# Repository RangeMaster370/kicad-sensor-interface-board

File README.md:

# SIB-1 sensor-interface board in KiCad

A small 2-layer board, designed in KiCad 7 and broken into four functional stages: (1) reverse-polarity protected 5 V input and 3.3 V LDO, (2) ATmega328P microcontroller with ISP and status LED, (3) ratiometric NTC front end with a Sallen–Key anti-alias filter, (4) I²C temperature sensor, calibration EEPROM, I²C and UART connectors. All symbols and footprints come from a custom library built for the board. The design is described once in `src/sib/design.py`; Python scripts generate the schematic, library, PCB and outputs with KiCad's own tools, and the tests check KiCad's exported netlist back against that description.

| Question | Method | Result (see `results/REPORT.md`) |
|---|---|---|
| Does the schematic say what the design says? | KiCad netlist export compared net-by-net with `design.py` | 0 differences over 22 nets and 15 no-connect pins |
| Would ERC flag anything? | ERC-style rules on the netlist (undriven power, single-pin nets, output conflicts) | 0 problems |
| Do symbols and footprints agree? | pin numbers vs pad numbers for all 36 placed parts | all match |
| Is the board manufacturable as drawn? | KiCad DRC (clearance 0.2 mm, edge 0.5 mm, courtyards, solder mask) | 0 errors, 0 warnings, 0 unconnected pads |
| How much routing? | Freerouting autorouter, GND pour on the bottom layer | 296 track segments, 35 vias, 698 mm of track |
| Why these parts? | component-selection table with requirement, choice, evidence, alternatives | 9 key parts, linked to the SPICE project results |

## Run

```sh
pip install -r requirements.txt   # plus KiCad 7, Java and Freerouting (see requirements.txt)
python3 -m unittest discover -s tests -v
python3 src/run_all.py            # regenerates hardware/ and results/ (about 40 s)
```

Open `hardware/sib.kicad_pro` in KiCad 7 or later to inspect or edit the schematic and PCB interactively.

## Structure

```
src/sib/design.py      parts, pin-to-net maps, stages, component-selection notes (single design source)
src/sib/symbols.py     custom symbol library (SIB.kicad_sym)
src/sib/footprints.py  custom footprint library (SIB.pretty) from package land-pattern dimensions
src/sib/schematic.py   hierarchical schematic: root + one sheet per functional stage
src/sib/checks.py      netlist comparison and ERC-style rules
src/sib/pcb.py         pcbnew placement by stage, Freerouting round trip, GND pour, DRC
src/run_all.py         full rebuild, Gerber/drill zip, BOM, renders, summary.json, REPORT.md
hardware/              KiCad project (schematic, PCB, library tables, library)
results/               schematic.pdf, BOM, component selection, DRC report, fabrication zip, plots
tests/                 13 checks
```

## Scope

Design and verification in KiCad only: the board has not been fabricated, assembled or bench-tested. Land patterns use nominal IPC-style dimensions for each package, and the autorouted layout favours completeness over hand-routed quality (see `docs/METHOD.md`). Companion projects: `sensor-frontend-spice-verification` (ngspice stage verification) and `avr-bringup-firmware-sim` (C bring-up firmware, simulated).

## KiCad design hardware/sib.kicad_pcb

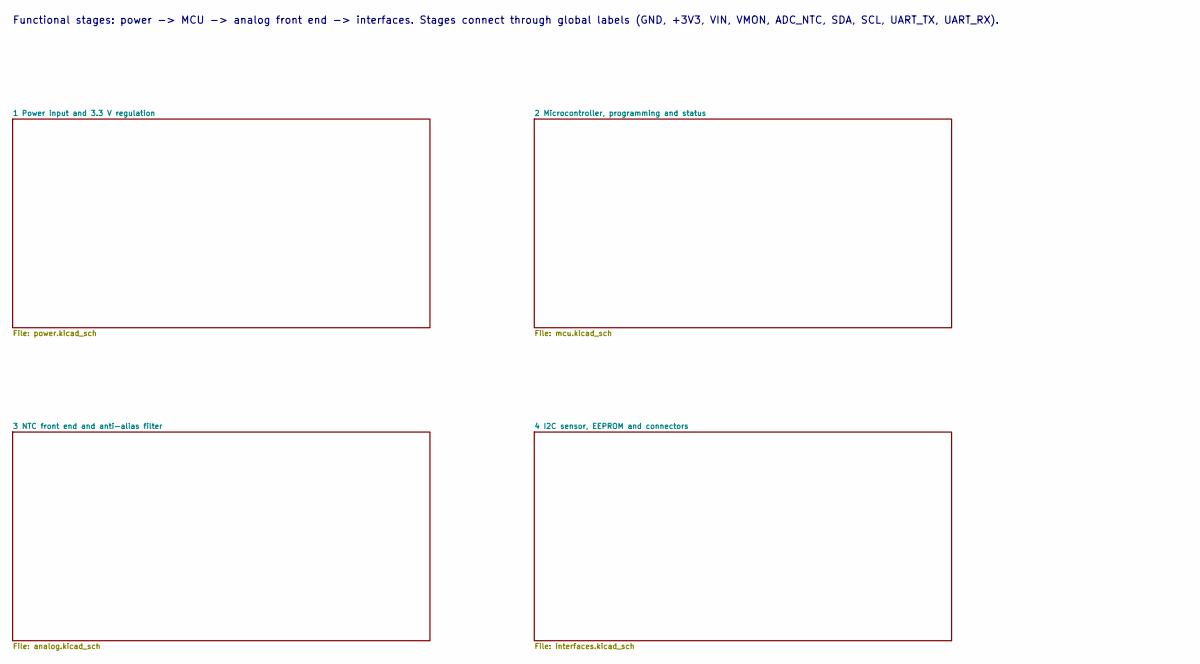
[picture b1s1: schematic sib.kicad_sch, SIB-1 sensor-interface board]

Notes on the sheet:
Functional stages: power -> MCU -> analog front end -> interfaces. Stages connect through global labels (GND, +3V3, VIN, VMON, ADC_NTC, SDA, SCL, UART_TX, UART_RX).

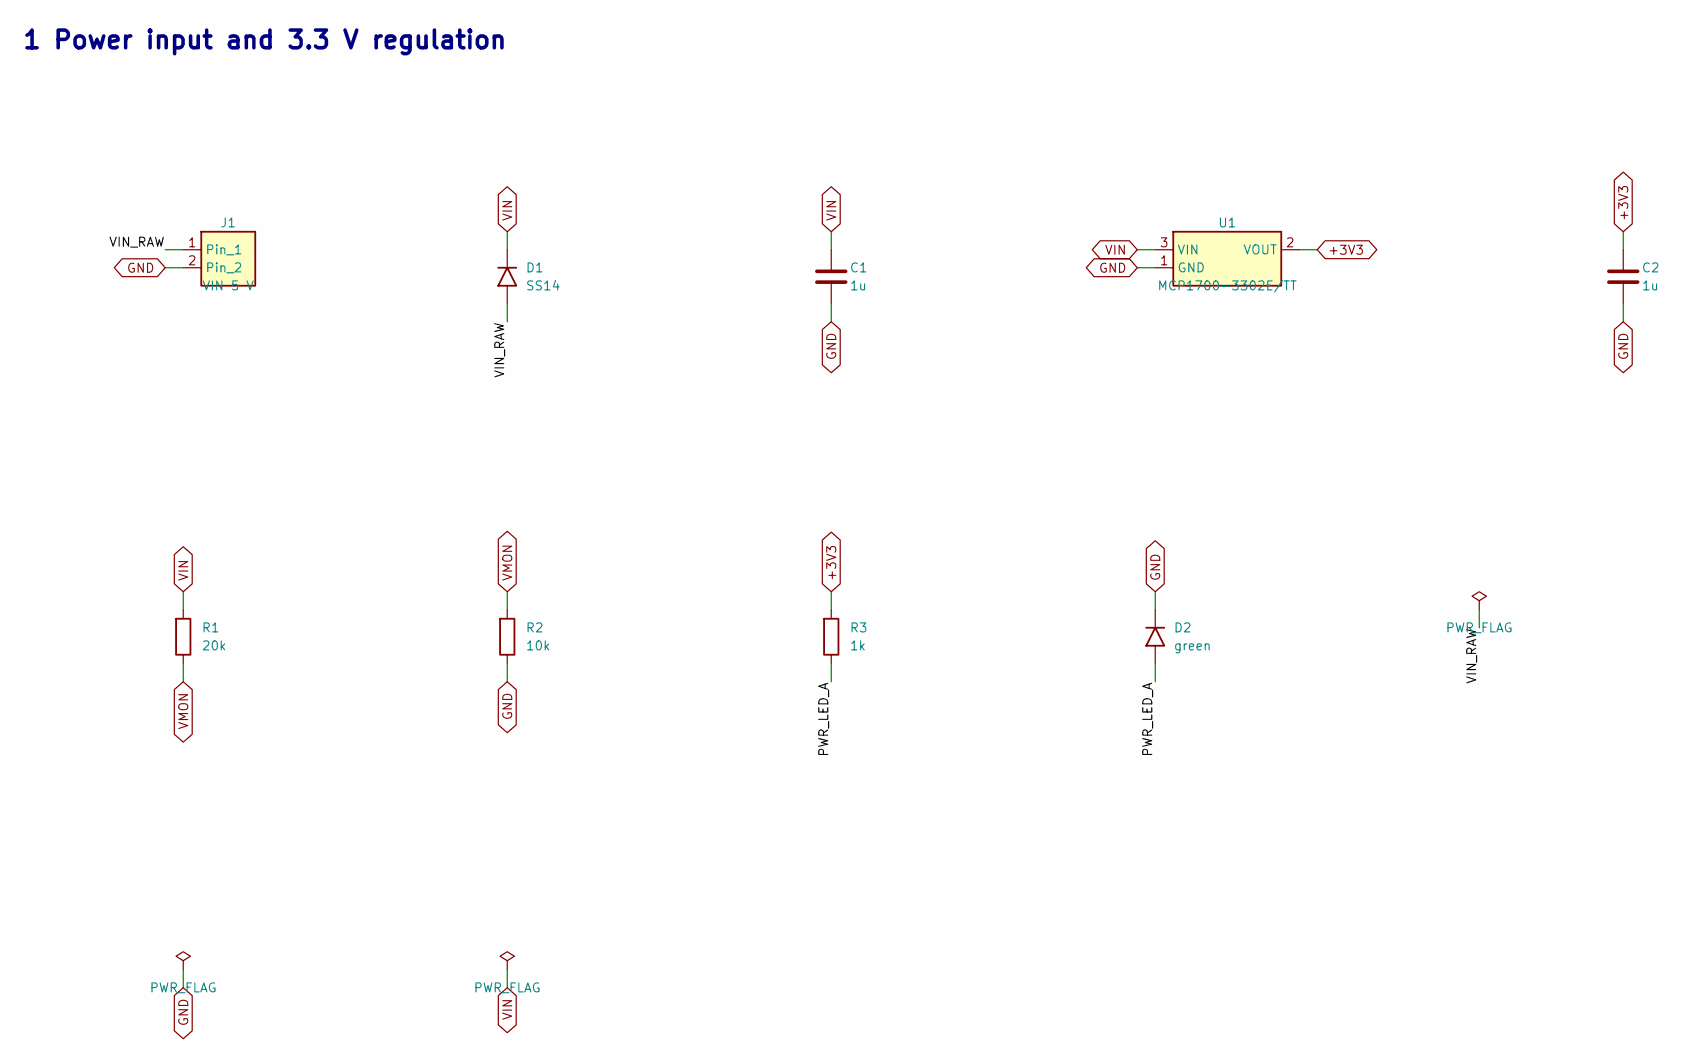
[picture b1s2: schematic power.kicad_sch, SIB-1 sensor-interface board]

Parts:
C1, C2: 1u; C_0603; MPN GRM188R61E105KA12
D1: SS14; D_SMA; MPN SS14
D2: green; LED_0603; MPN LTST-C191KGKT
J1: VIN 5 V; PinHeader_1x02_P2.54mm; MPN 2.54 mm header
R1: 20k; R_0603; MPN RC0603FR-0720KL
R2: 10k; R_0603; MPN RC0603FR-0710KL
R3: 1k; R_0603; MPN RC0603FR-071KL
U1: MCP1700-3302E/TT; SOT-23; MPN MCP1700T-3302E/TT

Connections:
+3V3: C2.1, R3.1, U1.2 (VOUT); also elsewhere on the board
GND: C1.2, C2.2, D2.1 (K), J1.2, R2.2, U1.1 (GND); also elsewhere on the board
PWR_LED_A: D2.2 (A), R3.2
VIN: C1.1, D1.1 (K), R1.1, U1.3 (VIN)
VIN_RAW: D1.2 (A), J1.1
VMON: R1.2, R2.1; also elsewhere on the board

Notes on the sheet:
1 Power input and 3.3 V regulation

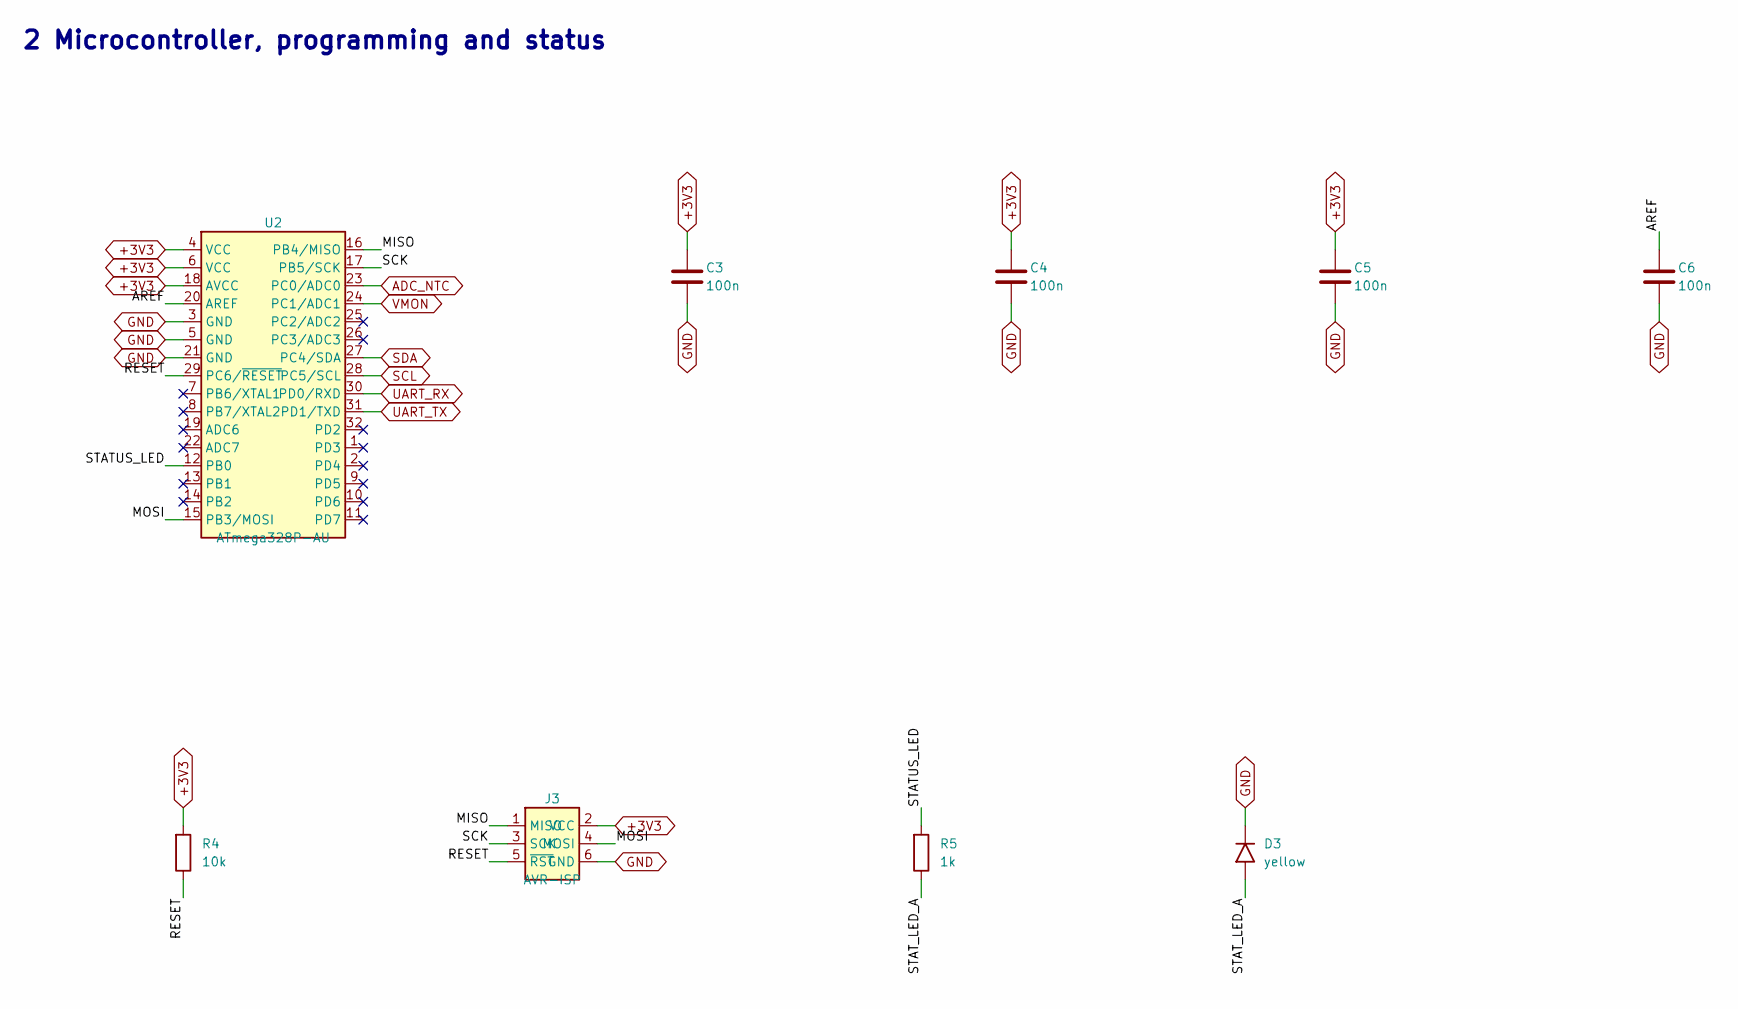
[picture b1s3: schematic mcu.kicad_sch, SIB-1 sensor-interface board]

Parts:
C3, C4, C5, C6: 100n; C_0603; MPN GRM188R71H104KA93
D3: yellow; LED_0603; MPN LTST-C191KSKT
J3: AVR-ISP; PinHeader_2x03_P2.54mm; MPN 2x3 header
R4: 10k; R_0603; MPN RC0603FR-0710KL
R5: 1k; R_0603; MPN RC0603FR-071KL
U2: ATmega328P-AU; TQFP-32_7x7mm_P0.8mm; MPN ATMEGA328P-AU

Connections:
+3V3: C3.1, C4.1, C5.1, J3.2 (VCC), R4.1, U2.4 (VCC), U2.6 (VCC), U2.18 (AVCC); also elsewhere on the board
ADC_NTC: U2.23 (PC0/ADC0); also elsewhere on the board
AREF: C6.1, U2.20 (AREF)
GND: C3.2, C4.2, C5.2, C6.2, D3.1 (K), J3.6 (GND), U2.3 (GND), U2.5 (GND), U2.21 (GND); also elsewhere on the board
MISO: J3.1 (MISO), U2.16 (PB4/MISO)
MOSI: J3.4 (MOSI), U2.15 (PB3/MOSI)
RESET: J3.5 (~RST), R4.2, U2.29 (PC6/~RESET)
SCK: J3.3 (SCK), U2.17 (PB5/SCK)
SCL: U2.28 (PC5/SCL); also elsewhere on the board
SDA: U2.27 (PC4/SDA); also elsewhere on the board
STATUS_LED: R5.1, U2.12 (PB0)
STAT_LED_A: D3.2 (A), R5.2
UART_RX: U2.30 (PD0/RXD); also elsewhere on the board
UART_TX: U2.31 (PD1/TXD); also elsewhere on the board
VMON: U2.24 (PC1/ADC1); also elsewhere on the board

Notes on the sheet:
2 Microcontroller, programming and status

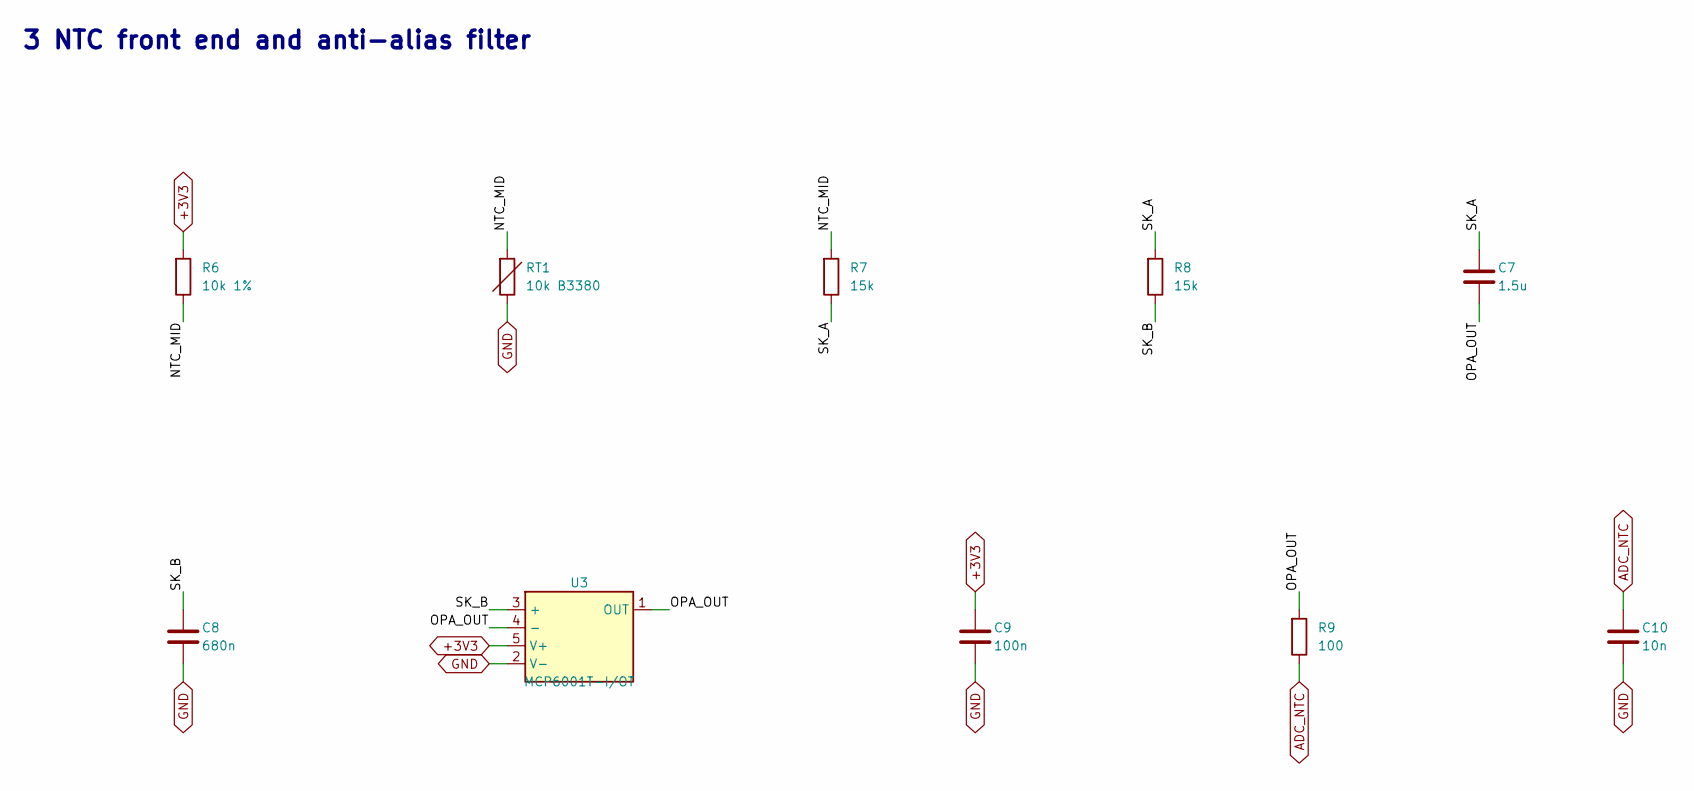
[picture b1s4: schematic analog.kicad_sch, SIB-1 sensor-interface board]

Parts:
C7: 1.5u; C_0805; MPN GRM21BR71C155KA01
C8: 680n; C_0603; MPN GRM188R71C684KA01
C9: 100n; C_0603; MPN GRM188R71H104KA93
C10: 10n; C_0603; MPN GRM188R71H103KA01
R6: 10k 1%; R_0603; MPN RC0603FR-0710KL
R7, R8: 15k; R_0603; MPN RC0603FR-0715KL
R9: 100; R_0603; MPN RC0603FR-07100RL
RT1: 10k B3380; R_0603; MPN NCP18XH103F03RB
U3: MCP6001T-I/OT; SOT-23-5; MPN MCP6001T-I/OT

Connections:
+3V3: C9.1, R6.1, U3.5 (V+); also elsewhere on the board
ADC_NTC: C10.1, R9.2; also elsewhere on the board
GND: C8.2, C9.2, C10.2, RT1.2, U3.2 (V-); also elsewhere on the board
NTC_MID: R6.2, R7.1, RT1.1
OPA_OUT: C7.2, R9.1, U3.1 (OUT), U3.4 (-)
SK_A: C7.1, R7.2, R8.1
SK_B: C8.1, R8.2, U3.3 (+)

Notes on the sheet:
3 NTC front end and anti-alias filter

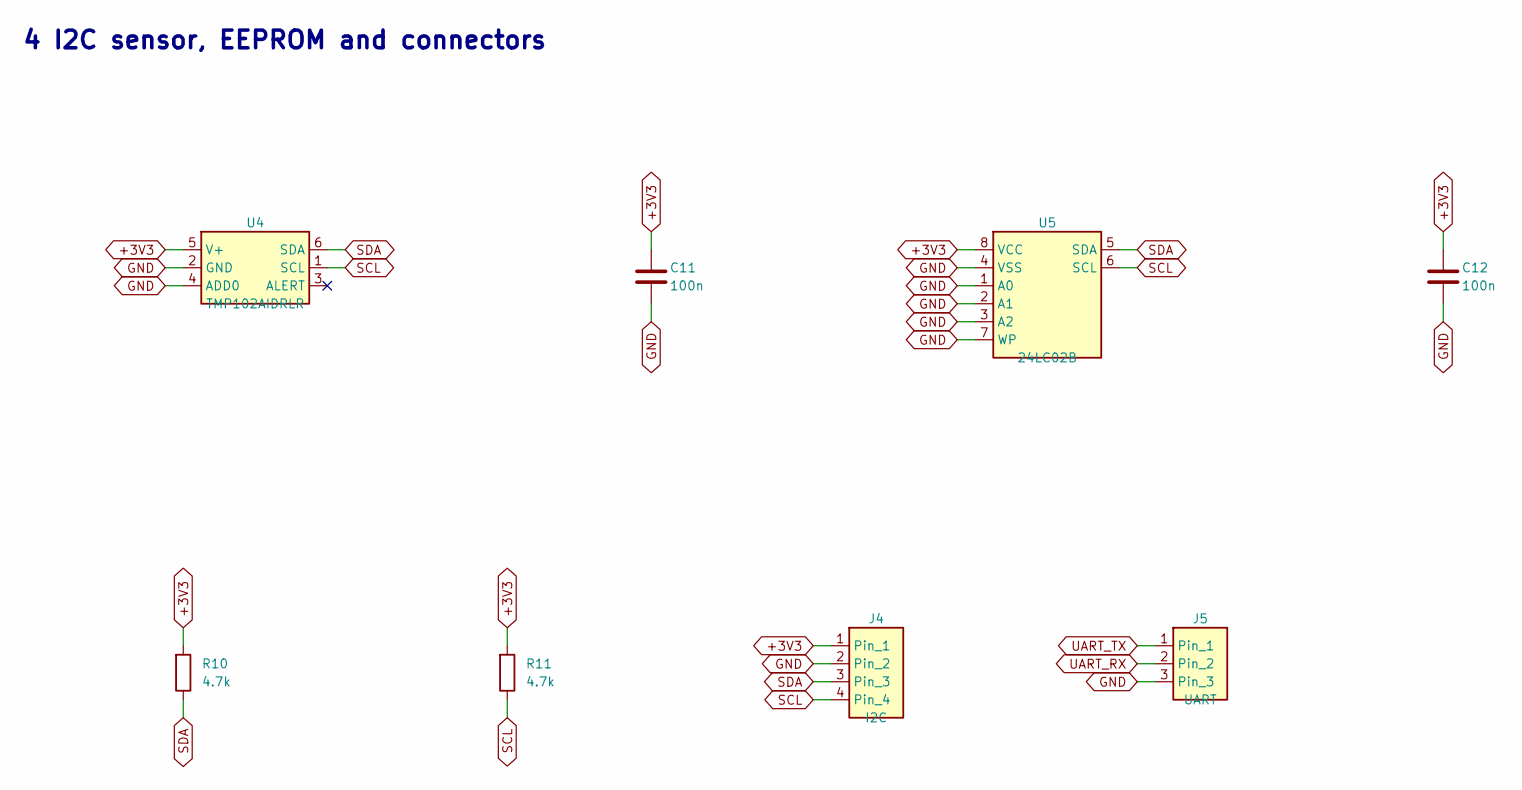
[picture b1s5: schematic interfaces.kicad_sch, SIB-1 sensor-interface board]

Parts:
C11, C12: 100n; C_0603; MPN GRM188R71H104KA93
J4: I2C; PinHeader_1x04_P2.54mm; MPN 2.54 mm header
J5: UART; PinHeader_1x03_P2.54mm; MPN 2.54 mm header
R10, R11: 4.7k; R_0603; MPN RC0603FR-074K7L
U4: TMP102AIDRLR; SOT-563; MPN TMP102AIDRLR
U5: 24LC02B; SOIC-8_3.9x4.9mm_P1.27mm; MPN 24LC02BT-I/SN

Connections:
+3V3: C11.1, C12.1, J4.1, R10.1, R11.1, U4.5 (V+), U5.8 (VCC); also elsewhere on the board
GND: C11.2, C12.2, J4.2, J5.3, U4.2 (GND), U4.4 (ADD0), U5.1 (A0), U5.2 (A1), U5.3 (A2), U5.4 (VSS), U5.7 (WP); also elsewhere on the board
SCL: J4.4, R11.2, U4.1 (SCL), U5.6 (SCL); also elsewhere on the board
SDA: J4.3, R10.2, U4.6 (SDA), U5.5 (SDA); also elsewhere on the board
UART_RX: J5.2; also elsewhere on the board
UART_TX: J5.1; also elsewhere on the board

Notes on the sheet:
4 I2C sensor, EEPROM and connectors

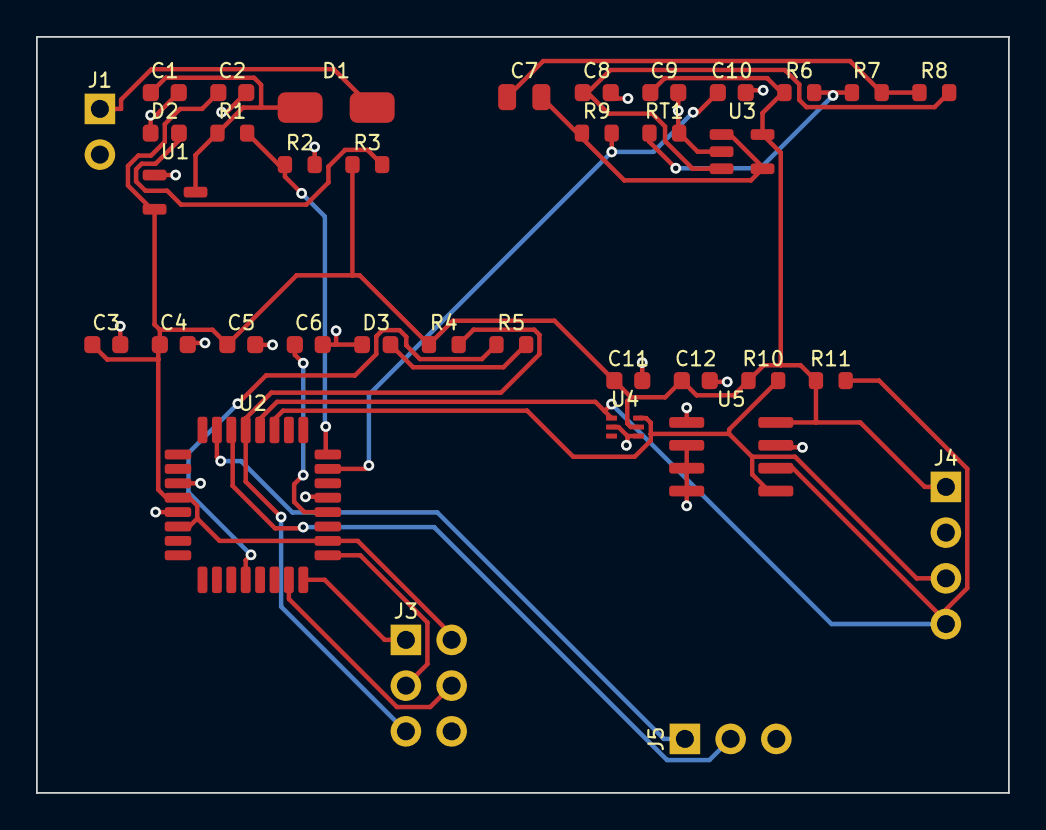
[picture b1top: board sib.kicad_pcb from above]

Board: 2 copper layers, 54.0 x 42.0 mm, 36 parts (0 on the bottom side), 22 nets.

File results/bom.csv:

refs,qty,value,footprint,mpn,stage,role
C1 C2,2,1u,C_0603,GRM188R61E105KA12,power,LDO input capacitor; LDO output capacitor
C10,1,10n,C_0603,GRM188R71H103KA01,analog,ADC charge reservoir
C3 C4 C5 C6 C9 C11 C12,7,100n,C_0603,GRM188R71H104KA93,mcu,VCC decoupling; AVCC decoupling; AREF capacitor; Op-amp decoupling; TMP102 decoupling; EEPROM decoupling
C7,1,1.5u,C_0805,GRM21BR71C155KA01,analog,Sallen-Key C1
C8,1,680n,C_0603,GRM188R71C684KA01,analog,Sallen-Key C2
D1,1,SS14,D_SMA,SS14,power,Reverse-polarity protection
D2,1,green,LED_0603,LTST-C191KGKT,power,Power LED
D3,1,yellow,LED_0603,LTST-C191KSKT,mcu,Status LED
J1,1,VIN 5 V,PinHeader_1x02_P2.54mm,2.54 mm header,power,Supply input
J3,1,AVR-ISP,PinHeader_2x03_P2.54mm,2x3 header,mcu,ISP programming
J4,1,I2C,PinHeader_1x04_P2.54mm,2.54 mm header,interfaces,I2C expansion
J5,1,UART,PinHeader_1x03_P2.54mm,2.54 mm header,interfaces,UART debug port
R1,1,20k,R_0603,RC0603FR-0720KL,power,Supply monitor divider top
R10 R11,2,4.7k,R_0603,RC0603FR-074K7L,interfaces,SDA pull-up; SCL pull-up
R2 R4,2,10k,R_0603,RC0603FR-0710KL,power,Supply monitor divider bottom; Reset pull-up
R3 R5,2,1k,R_0603,RC0603FR-071KL,power,Power LED resistor; Status LED resistor
R6,1,10k 1%,R_0603,RC0603FR-0710KL,analog,NTC divider top
R7 R8,2,15k,R_0603,RC0603FR-0715KL,analog,Sallen-Key R1; Sallen-Key R2
R9,1,100,R_0603,RC0603FR-07100RL,analog,Isolation resistor
RT1,1,10k B3380,R_0603,NCP18XH103F03RB,analog,Board temperature sensor
U1,1,MCP1700-3302E/TT,SOT-23,MCP1700T-3302E/TT,power,3.3 V LDO
U2,1,ATmega328P-AU,TQFP-32_7x7mm_P0.8mm,ATMEGA328P-AU,mcu,Microcontroller
U3,1,MCP6001T-I/OT,SOT-23-5,MCP6001T-I/OT,analog,Buffer op-amp
U4,1,TMP102AIDRLR,SOT-563,TMP102AIDRLR,interfaces,"Digital temperature sensor, address 0x48"
U5,1,24LC02B,SOIC-8_3.9x4.9mm_P1.27mm,24LC02BT-I/SN,interfaces,"Calibration EEPROM, address 0x50"

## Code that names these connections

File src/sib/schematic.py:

"""Generate the hierarchical KiCad 7 schematic: a root sheet plus one sheet per functional stage.

Each pin gets a short wire stub ending in a net label (local within a stage, global between
stages) or a no-connect marker. KiCad's own netlist export is then compared with design.py.
"""
from __future__ import annotations

import math
import uuid
from pathlib import Path

from . import design, symbols

NS = uuid.UUID("5b1a1d1e-0000-4000-8000-0000000051b1")
PROJECT = "sib"
G = 1.27
STUB = 2.54
FONT = "(effects (font (size 1.27 1.27)))"
HIDE = "(effects (font (size 1.27 1.27)) hide)"


def uid(*key) -> str:
    return str(uuid.uuid5(NS, "/".join(map(str, key))))


def snap(v: float) -> float:
    return round(round(v / G) * G, 4)


ROOT_UUID = uid("root")
SHEET_UUID = {name: uid("sheet", name) for name, _ in design.SHEETS}


class SheetWriter:
    def __init__(self, sheet: str, syms: dict):
        self.sheet, self.syms, self.items, self.used = sheet, syms, [], {}

    def wire(self, a, b):
        self.items.append(f'(wire (pts (xy {a[0]:g} {a[1]:g}) (xy {b[0]:g} {b[1]:g})) '
                          f'(stroke (width 0) (type default)) (uuid {uid(self.sheet, "w", a, b)}))')

    def label(self, net, at, out):
        ang, just = {(-1, 0): (180, "right"), (1, 0): (0, "left"), (0, -1): (90, "left"), (0, 1): (270, "right")}[out]
        if net in design.GLOBAL_NETS:
            self.items.append(
                f'(global_label "{net}" (shape bidirectional) (at {at[0]:g} {at[1]:g} {ang}) (fields_autoplaced) '
                f'(effects (font (size 1.27 1.27)) (justify {just})) (uuid {uid(self.sheet, "gl", net, at)}) '
                f'(property "Intersheetrefs" "${{INTERSHEET_REFS}}" (at {at[0]:g} {at[1]:g} 0) {HIDE}))')
        else:
            self.items.append(f'(label "{net}" (at {at[0]:g} {at[1]:g} {ang}) (fields_autoplaced) '
                              f'(effects (font (size 1.27 1.27)) (justify {just} bottom)) '
                              f'(uuid {uid(self.sheet, "l", net, at)}))')

    def no_connect(self, at):
        self.items.append(f'(no_connect (at {at[0]:g} {at[1]:g}) (uuid {uid(self.sheet, "nc", at)}))')

    def place(self, part: design.Part, sx: float, sy: float):
        _, pin_pos = self.syms[part.symbol]
        self.used[part.symbol] = True
        ys = [-p[1] for p in pin_pos.values()]
        top = sy + min(ys) - 2 * G
        props = [("Reference", part.ref, (sx, snap(top - G)), part.ref.startswith("#")),
                 ("Value", part.value, (sx, snap(sy + max(ys) + 2 * G)), False),
                 ("Footprint", f"SIB:{part.footprint}" if part.footprint else "", (sx, sy), True),
                 ("Datasheet", "", (sx, sy), True),
                 ("MPN", part.mpn, (sx, sy), True)]
        if len(pin_pos) == 2 and part.symbol != "Conn_01x02":
            props[0] = ("Reference", part.ref, (snap(sx + 2.54), snap(sy - G)), part.ref.startswith("#"))
            props[1] = ("Value", part.value, (snap(sx + 2.54), snap(sy + G)), False)
        ptxt = " ".join(
            f'(property "{k}" "{v}" (at {x:g} {y:g} 0) '
            f'{HIDE if hidden else ("(effects (font (size 1.27 1.27)) (justify left))" if len(pin_pos) == 2 and k in ("Reference", "Value") and part.symbol != "Conn_01x02" else FONT)})'
            for k, v, (x, y), hidden in props)
        pins = " ".join(f'(pin "{n}" (uuid {uid(self.sheet, part.ref, "pin", n)}))' for n in pin_pos)
        in_bom = "yes" if part.in_bom else "no"
        on_board = "no" if part.ref.startswith("#") else "yes"
        self.items.append(
            f'(symbol (lib_id "SIB:{part.symbol}") (at {sx:g} {sy:g} 0) (unit 1) (in_bom {in_bom}) '
            f'(on_board {on_board}) (dnp no) (fields_autoplaced) (uuid {uid(self.sheet, part.ref)}) {ptxt} {pins} '
            f'(instances (project "{PROJECT}" (path "/{ROOT_UUID}/{SHEET_UUID[self.sheet]}" '
            f'(reference "{part.ref}") (unit 1)))))')
        for num, (px, py, ang) in pin_pos.items():
            end = (snap(sx + px), snap(sy - py))
            out = (-round(math.cos(math.radians(ang))), round(math.sin(math.radians(ang))))
            net = part.pins.get(num)
            if net is None:
                self.no_connect(end)
                continue
            tip = (snap(end[0] + out[0] * STUB), snap(end[1] + out[1] * STUB))
            self.wire(end, tip)
            self.label(net, tip, out)

    def text(self, s, at, size=2.0):
        self.items.append(f'(text "{s}" (at {at[0]:g} {at[1]:g} 0) '
                          f'(effects (font (size {size:g} {size:g}) bold) (justify left bottom)) '
                          f'(uuid {uid(self.sheet, "t", s)}))')

    def render(self, title: str) -> str:
        lib = "\n    ".join(symbols.all_symbols(prefix="SIB:")[n][0] for n in sorted(self.used))
        return (f'(kicad_sch (version 20230121) (generator sib_schgen)\n  (uuid {SHEET_UUID[self.sheet]})\n'
                f'  (paper "A4")\n  (title_block (title "SIB-1 sensor-interface board") (comment 1 "{title}"))\n'
                f'  (lib_symbols\n    {lib}\n  )\n  ' + "\n  ".join(self.items) + "\n)\n")


def _extent(pin_pos):
    xs = [p[0] for p in pin_pos.values()]
    ys = [-p[1] for p in pin_pos.values()]
    return min(xs), max(xs), min(ys), max(ys)


def layout_sheet(sheet: str, title: str, syms) -> str:
    w = SheetWriter(sheet, syms)
    w.text(title, (15.24, 22.86), 2.5)
    x, y, row_h = 15.24, 30.48, 0.0
    x_max = 270.0
    for part in [p for p in design.PARTS if p.sheet == sheet]:
        x0, x1, y0, y1 = _extent(syms[part.symbol][1])
        width = (x1 - x0) + 2 * 22.86            # room for labels on both sides
        height = (y1 - y0) + 43.18              # stubs plus vertical labels above and below
        if x + width > x_max:
            x, y, row_h = 15.24, y + row_h, 0.0
        sx, sy = snap(x - x0 + 22.86), snap(y - y0 + 20.32)
        w.place(part, sx, sy)
        x += width
        row_h = max(row_h, height)
    return w.render(title)


def root_sheet() -> str:
    items = []
    for i, (name, title) in enumerate(design.SHEETS):
        x, y = 50.8 + (i % 2) * 127.0, 63.5 + (i // 2) * 76.2
        items.append(
            f'(sheet (at {x:g} {y:g}) (size 101.6 50.8) (fields_autoplaced) (stroke (width 0.1524) (type solid)) '
            f'(fill (color 0 0 0 0.0000)) (uuid {SHEET_UUID[name]}) '
            f'(property "Sheetname" "{title}" (at {x:g} {y - 0.7:g} 0) (effects (font (size 1.27 1.27)) (justify left bottom))) '
            f'(property "Sheetfile" "{name}.kicad_sch" (at {x:g} {y + 51.4:g} 0) (effects (font (size 1.27 1.27)) (justify left top))) '
            f'(instances (project "{PROJECT}" (path "/{ROOT_UUID}" (page "{i + 2}")))))')
    note = ("(text \"Functional stages: power -> MCU -> analog front end -> interfaces. Stages connect through global "
            f"labels (GND, +3V3, VIN, VMON, ADC_NTC, SDA, SCL, UART_TX, UART_RX).\" (at 50.8 40.64 0) "
            f"(effects (font (size 1.778 1.778)) (justify left bottom)) (uuid {uid('root', 'note')}))")
    return (f'(kicad_sch (version 20230121) (generator sib_schgen)\n  (uuid {ROOT_UUID})\n  (paper "A4")\n'
            f'  (title_block (title "SIB-1 sensor-interface board") (date "2026-10-06") (rev "A") '
            f'(comment 1 "Generated from src/sib/design.py"))\n  (lib_symbols)\n  {note}\n  '
            + "\n  ".join(items) + '\n  (sheet_instances (path "/" (page "1")))\n)\n')


def write(folder: Path):
    syms = symbols.all_symbols()
    (folder / f"{PROJECT}.kicad_sch").write_text(root_sheet())
    for name, title in design.SHEETS:
        (folder / f"{name}.kicad_sch").write_text(layout_sheet(name, title, syms))
    (folder / "sym-lib-table").write_text(
        '(sym_lib_table\n  (lib (name "SIB")(type "KiCad")(uri "${KIPRJMOD}/lib/SIB.kicad_sym")(options "")(descr "SIB-1 custom symbols"))\n)\n')
    (folder / "fp-lib-table").write_text(
        '(fp_lib_table\n  (lib (name "SIB")(type "KiCad")(uri "${KIPRJMOD}/lib/SIB.pretty")(options "")(descr "SIB-1 custom footprints"))\n)\n')
